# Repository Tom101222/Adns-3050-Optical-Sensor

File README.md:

# Adns-3050-Optical-Sensor
Library and Eagle cad files for the Adns-3050 Sensor

Boards are now avaible for purchase on tindie! https://www.tindie.com/products/tom10122/adns-3050-optical-sensor-board/

Overview

The ADNS 3050 is an entry level gaming sensor with up to 2000cpi resolution. It uses 6 wires to communicate via SPI(including Power) and can be used to create your own computer mouse in addition to other uses in robotics. 

Setup

Wiring
The pins used in the program are defined at the top of the header file.

MOSI -- MOSI, 

MISO -- MISO, 

SCLK -- SCLK, 

NCS -- 3 (any pin you want)

Software

A method has been provided to automate the setup of the sensor. It does not require as much setup as the adns-9800 laser based sensor. The default setup method (startup) uses all the default configuration options for the sensor but they can be changed easily. All configuration is done by writing to the correct registers on the sensor, a quick look over the datasheet should help anyone looking to change some settings, the write method can be used to write to the settings to the registers.  

Using to obtain postion

Once the startup method has been run it is easy to obtain the position of the sensor, just use getx() and gety() consecutively, it is important that there are no read operations between the two otherwise the data will be corrupted or changed.  

Sensor Operation

The ADNS 3050 is essentially a small camera. It takes consecutive photos and the DSP mathematically determines the amount of movement between pictures. The data is then stored in the DELTA_X and DELTA_Y registers (0X03 and 0X04 respectively) Once the the registers are read they are re-written with new data.

Setting the Resolution 

Resolution is determined by the value of bits 4-2 in the MOUSE_CNTRL register (0x0d). By default this is set to 1000 cpi. To change the resolution just write to the register with the corresponding value . For example, to set the resolution to 2000 cpi  just use:

Write(0x0d,B11000);

This sets bits 4-2 to 110 and bits 1 and 0 to 0 (needed for operation).  110 corresponds with the value found on page 29 of the datasheet for a resolution of 2000 

Lift off detection 

The sensor will stop tracking if the SQUAL is too low (usually when the sensor is too far off the ground). Sometimes when the sensor is placed back down it will not wake up. To mitigate/disable liftoff detection you can set the SQUAL_Threshold to 0 in the MISC_Settings register.The following code does just that:

Write(0x25,B0000001);

This should be run during setup.

Any questions or comments feel free to email me at twigg1012@gmail.com

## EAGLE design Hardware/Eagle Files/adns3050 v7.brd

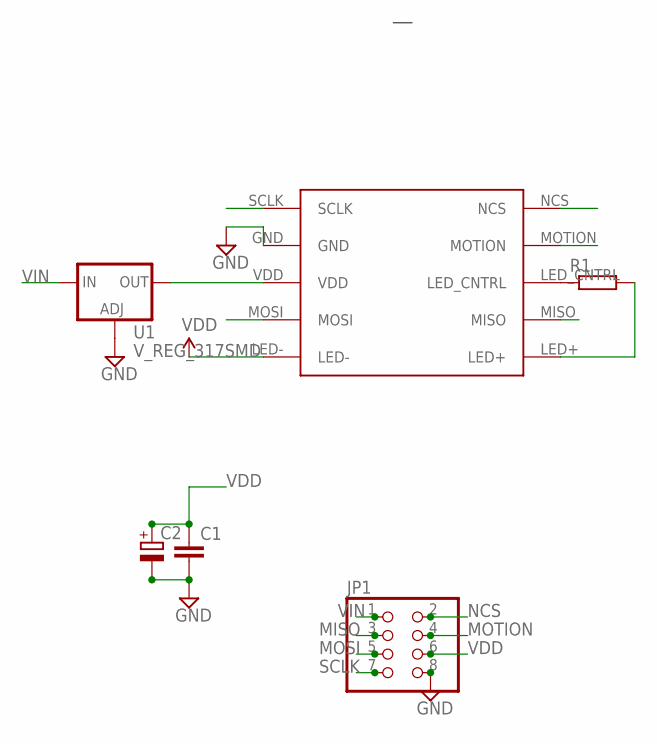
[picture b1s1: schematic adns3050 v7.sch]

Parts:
C1: CC0603; C0603
C2: CPOL-EUR/2012-12R; R/2012-12R
JP1: PINHD-2X4; 2X04
R1: RR0603; R0603
U1: V_REG_317SMD; SOT223
U$1: 3050; ADNS3

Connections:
GND: C1.2, C2.-, JP1.8, U1.1 (ADJ), U$1.GND
MISO: JP1.3, U$1.MISO
MOSI: JP1.5, U$1.MOSI
MOTION: JP1.4, U$1.MOTION
unnamed: R1.1, U$1.LED_CNTRL
unnamed: R1.2, U$1.LED+
NCS: JP1.2, U$1.NCS
SCLK: JP1.7, U$1.SCLK
VDD: C1.1, C2.+, JP1.6, U1.2 (OUT), U$1.LED-, U$1.VDD
VIN: JP1.1, U1.3 (IN)

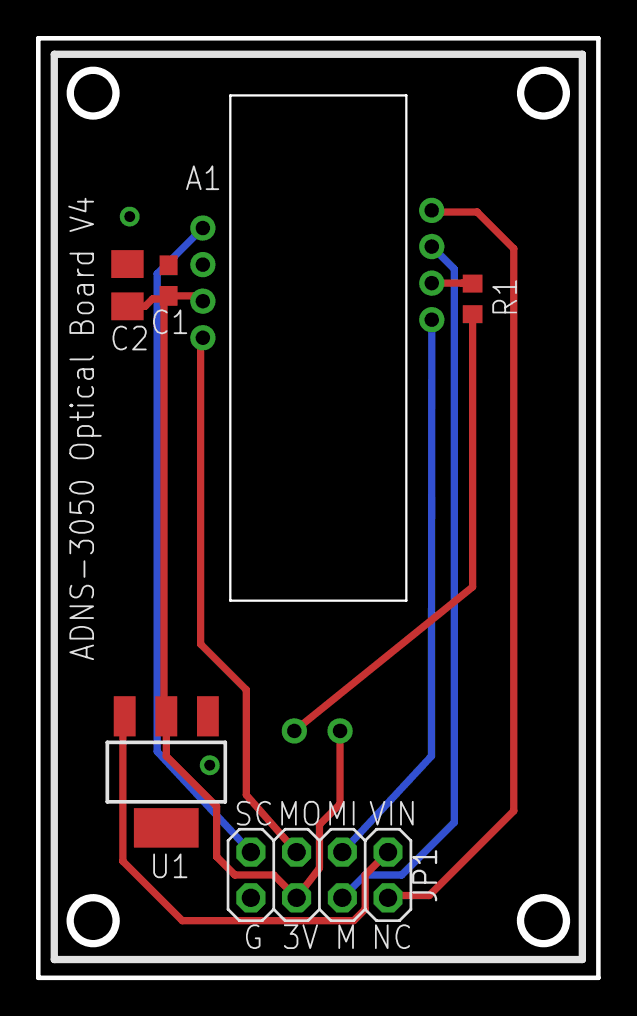
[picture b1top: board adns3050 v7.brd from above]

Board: 2 copper layers, 31.0 x 52.0 mm, 6 parts (0 on the bottom side), 10 nets.

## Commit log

2016-08-23 :space_invader: Added .gitattributes & .gitignore files
2016-08-23 Added Hardware and edited readme
2016-08-23 Added Gerber Files
2016-08-25 Added components
2016-09-07 Updated board, increased text spacing
2016-11-14 Updated Gerbers + Documentation
2016-11-15 Added Models
2016-11-16 Formatting Changes

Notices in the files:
parts and their libraries:
SparkFun-PowerIC: Licensing: Creative Commons ShareAlike 4.0 International - https://creativecommons.org/licenses/by-sa/4.0
